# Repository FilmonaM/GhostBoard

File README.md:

# GhostBoard

A 66‑key custom, hot‑swappable mechanical keyboard built around the RP2040 MCU and a USB‑C port.

## Key Features
- **Hot‑swappable sockets** (MX) allow you to change switches whenever you want without soldering.  
- Compact 66‑key layout inspired by Keychron’s design.  
- Fully two‑layer PCB with bottom‑side routing for a clean top surface.  

## Layout
Here’s the final Keyboard Layout Editor (KLE) grid I used for my 66‑key design:

## PCB
After routing all rows and columns on the bottom layer and placing 66 hot‑swap footprints on top, this is the final PCB:

## Case & CAD
The case was made in onshape and includes a cutout for the usbc port:

## BOM

| Components                     | Quantity | Price (USD) | Link                                      |
|--------------------------------|----------|-------------|-------------------------------------------|
|all the discrete components| bulk     | around $10 USD   | all from JLCPCB|
| Hot‑swap sockets (Cherry MX)   | 66       | $14 USD       | [from amazon](https://www.amazon.com/DUROCK-Mechanical-Keyboard-Switches-Hot-Swap/dp/B0B4W9YMGM?th=1)                                     |
| Cherry MX Brown switches       | 66       | $50 USD       | [from amazaon](https://www.amazon.com/Switches-Mechanical-Keyboards-Mounted-MX1AG1NA/dp/B09ZSR5WKH/ref=sr_1_1?crid=25HJUXP1OSN6J&dib=eyJ2IjoiMSJ9.JCXKItNl7G_bBJpSwKUJq664n-BOf2YbUH0WZa7hDmZxRafbLwI-glj977bGbt29tDvCveNze3P3gqmgoAn0l3rlchmQZ61RmHV2XPem3Jz3tot1azwV7jrsNV-PzRqVyuHCwUeeXaebcL0bObmG1d8kziBrCC7ZMtnRtgIo-ddwnsvz2wgowiUgUF-HD41rfdkHTE_UOYzvFpoSButMwc7_yddFstvRSoyNQbJw2ynUmxFPIG3dxOFQfZoTBf_ieIKHUoq1lWhQpLDM12rkFp4_vQ0Xz3IjDz0DVBT-efY.RL9APB_ELO4EKoe-h864Dvl7o-cF4AvWYBAotoN6pFo&dib_tag=se&keywords=cherry%2Bmx%2Bswitches%2Bbrown&qid=1753349383&s=electronics&sprefix=cherry%2Bmx%2Bswitches%2Bbrow%2Celectronics%2C191&sr=1-1&th=1)                                    |
| Stabilizer kit                 | 1        | $19 USD       | [from amazon](https://www.amazon.com/Keyboard-Stabilizers-Mechanical-Keyboards-Switches/dp/B0D2R13N2N/ref=sr_1_1_sspa?crid=2UC7ED8DWWUDM&dib=eyJ2IjoiMSJ9.P4sTVbDzkYqSr2Qe2aEKgUz9OjRmws6DREJdi517d7j9yxmY-mCmIoPxXbUmOFQNayDjFH5Sx7xpnLaN4KOjDOL0SpdCwoeUz22PRWkEPbsXPuUcYROyJJAhYlPQDTz6njqvp06jBaKfk85rN3X2qAGkjYN52kWKGrqK5ZmzdgV61Xb8_8AqggnEFYknCTHt.kM48GyCD-8_UloBzSZMtd7l1z-blnw8Z4I1GEPk9-0M&dib_tag=se&keywords=mx%2Bstabs&qid=1753349468&s=electronics&sprefix=mx%2Bstabs%2Celectronics%2C166&sr=1-1-spons&sp_csd=d2lkZ2V0TmFtZT1zcF9hdGY&th=1)
| RP2040 MCU board- usbc           | 1        | $1.20        | [amazon link](https://www.amazon.com/RP2040-Board-Type-C-Raspberry-Micropython/dp/B0CG9FWDDC?th=1) |
| PCBs (×5, incl. shipping & tax) | 5        | $29.29       | using jlcpcb                               |

total price = $119.49

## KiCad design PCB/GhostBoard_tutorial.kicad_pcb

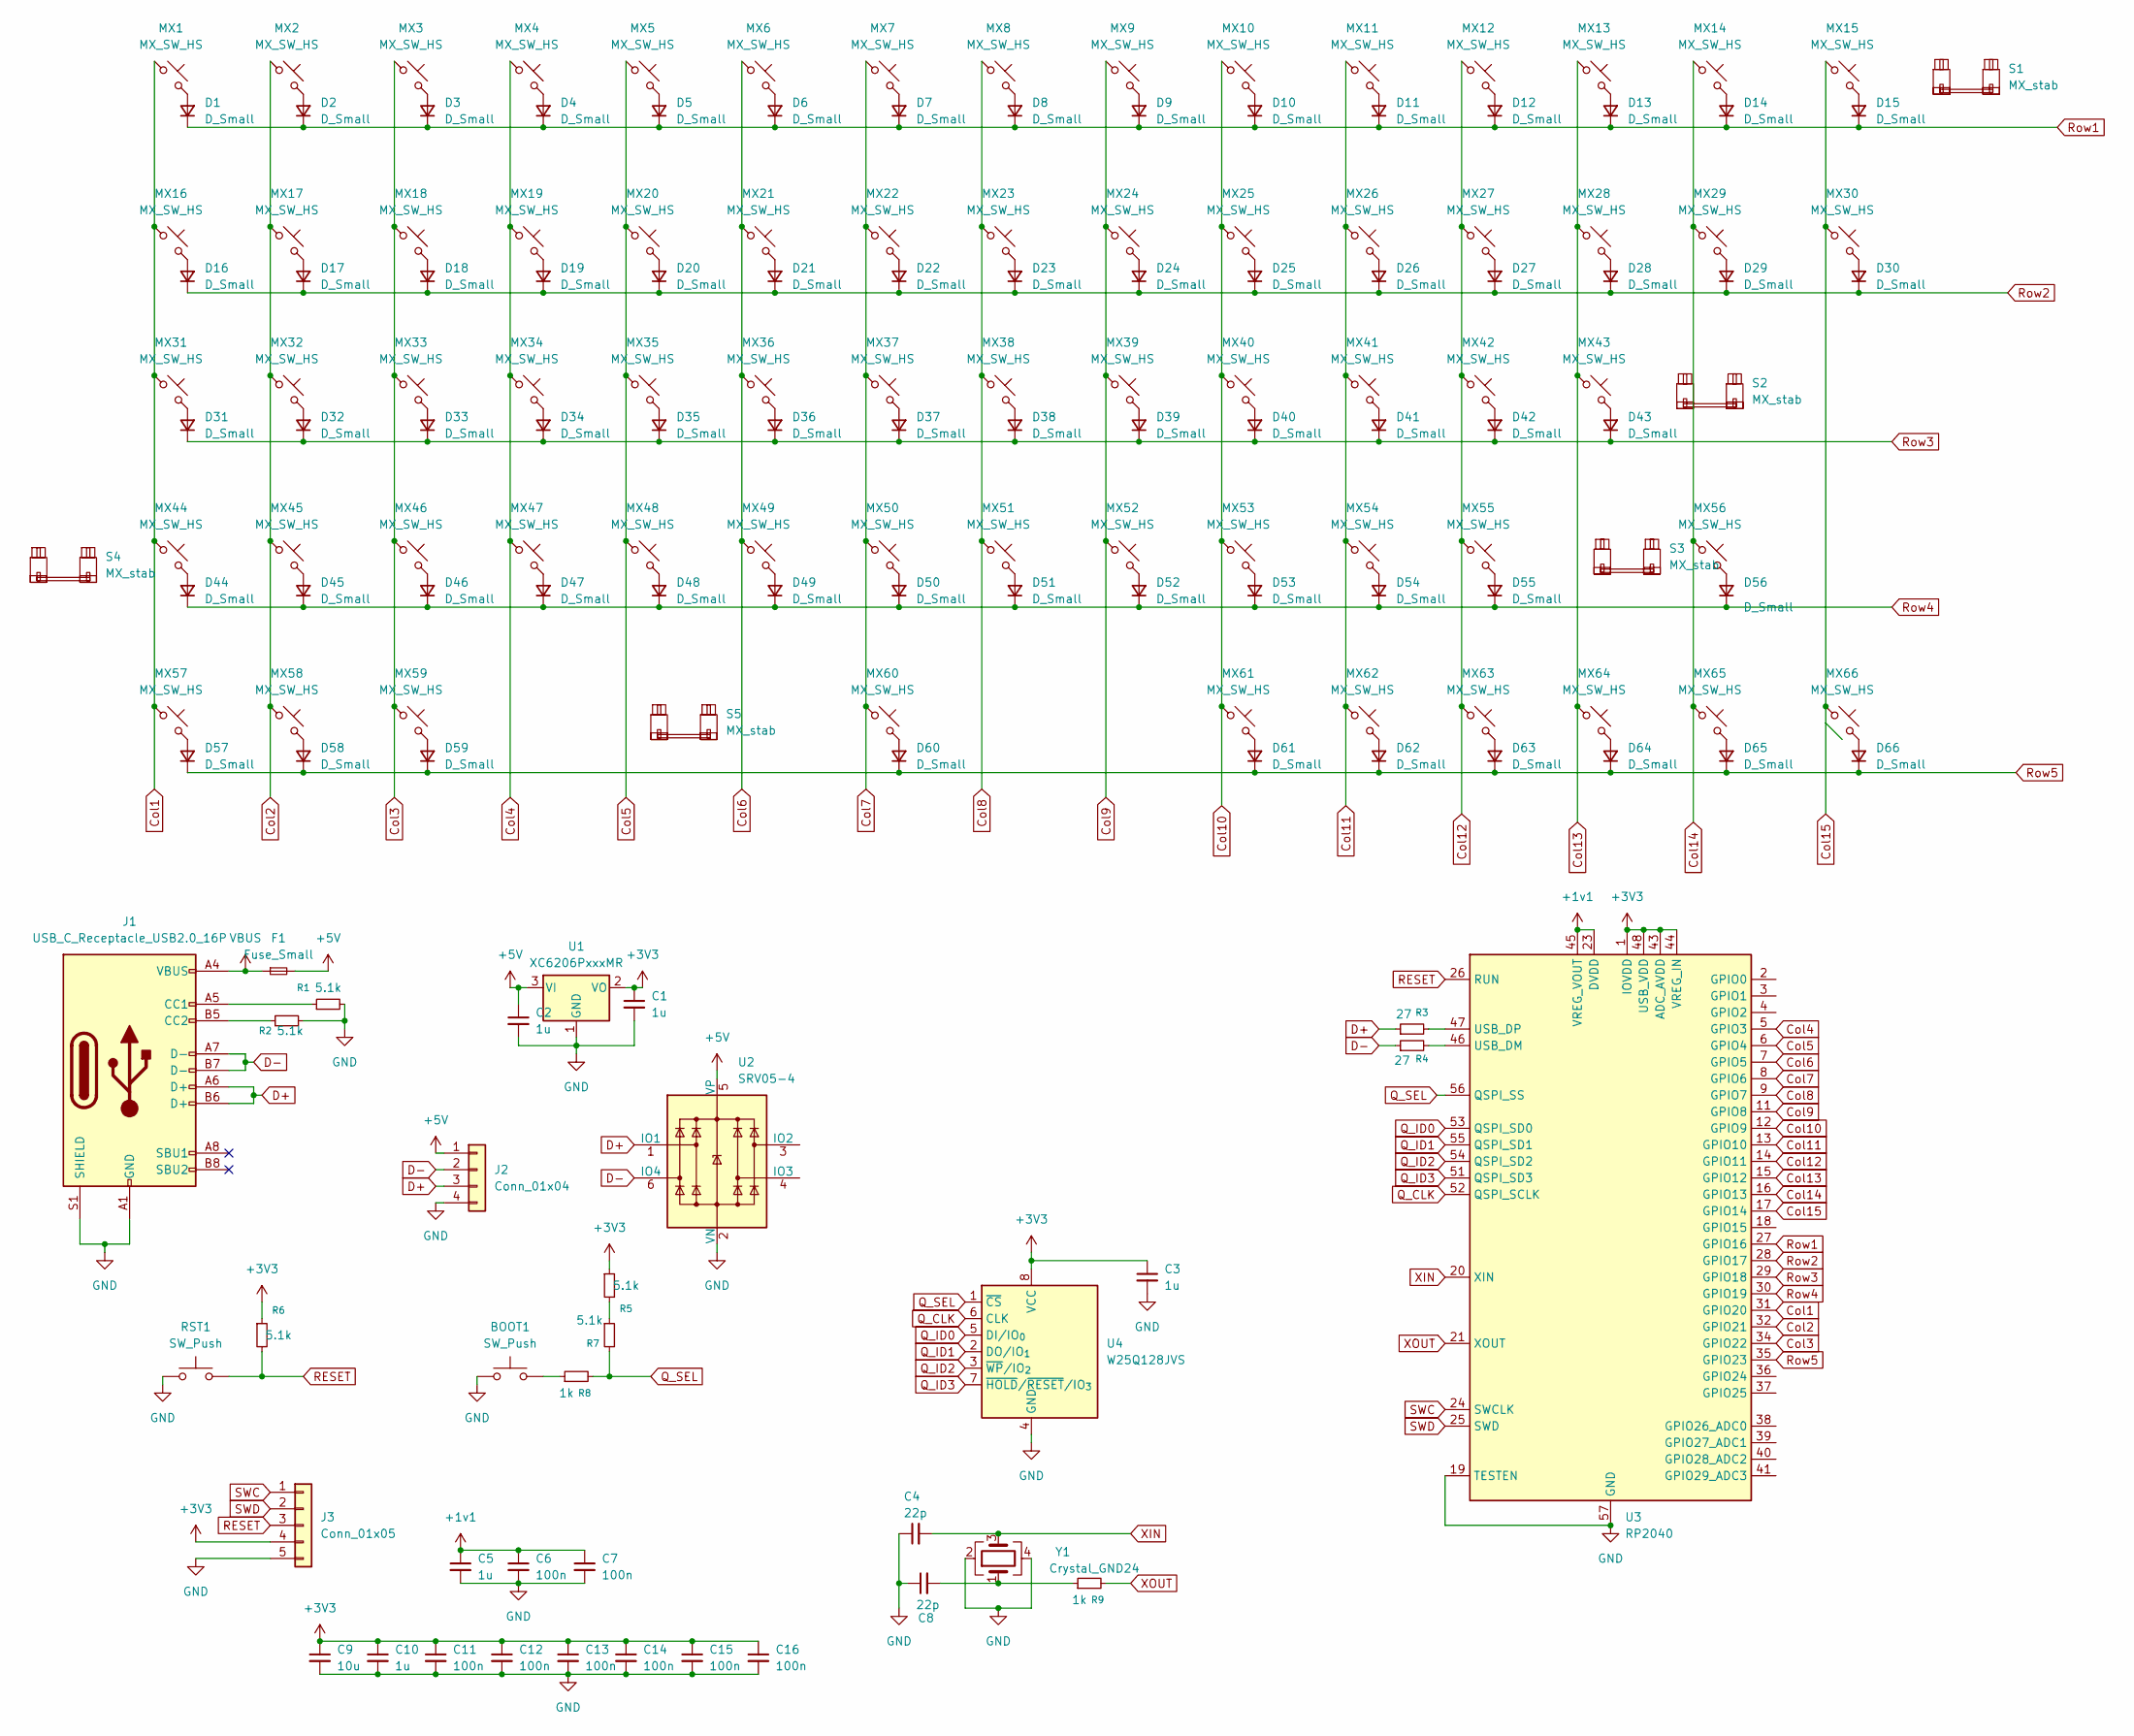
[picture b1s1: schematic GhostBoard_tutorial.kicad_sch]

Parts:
BOOT1: SW_Push; SW_SPST_TL3342
C1, C2, C3, C5, C10: 1u; C_0402_1005Metric
C4, C8: 22p; C_0402_1005Metric
C6, C7, C11, C12, C13, C14, C15, C16: 100n; C_0402_1005Metric
C9: 10u; C_0603_1608Metric
D1, D2, D3, D4, D5, D6, D7, D8, D9, D10, D11, D12, D13, D14, D15, D16, D17, D18, D19, D20, D21, D22, D23, D24, D25, D26, D27, D28, D29, D30, D31, D32, D33, D34, D35, D36, D37, D38, D39, D40, D41, D42, D43, D44, D45, D46, D47, D48, D49, D50, D51, D52, D53, D54, D55, D56, D57, D58, D59, D60, D61, D62, D63, D64, D65, D66: D_Small; D_SOD-123
F1: Fuse_Small; Fuse_1206_3216Metric
J1: USB_C_Receptacle_USB2.0_16P; USB_C_Receptacle_HRO_TYPE-C-31-M-12
J2: Conn_01x04; JST_SH_SM04B-SRSS-TB_1x04-1MP_P1.00mm_Horizontal
J3: Conn_01x05; PinHeader_1x05_P2.54mm_Vertical
MX1, MX2, MX3, MX4, MX5, MX6, MX7, MX8, MX9, MX10, MX11, MX12, MX13, MX14, MX15, MX17, MX18, MX19, MX20, MX21, MX22, MX23, MX24, MX25, MX26, MX27, MX28, MX30, MX32, MX33, MX34, MX35, MX36, MX37, MX38, MX39, MX40, MX41, MX42, MX43, MX44, MX45, MX46, MX47, MX48, MX49, MX50, MX51, MX52, MX53, MX54, MX55, MX56, MX58, MX60, MX64, MX65, MX66: MX_SW_HS; SW_MX_HS_CPG151101S11_1u
MX16, MX29: MX_SW_HS; SW_MX_HS_CPG151101S11_1.5u
MX31: MX_SW_HS; SW_MX_HS_CPG151101S11_1.75u
MX57, MX59, MX61, MX62, MX63: MX_SW_HS; SW_MX_HS_CPG151101S11_1.25u
R1, R2, R5, R6, R7: 5.1k; R_0402_1005Metric
R3, R4: 27; R_0402_1005Metric
R8, R9: 1k; R_0402_1005Metric
RST1: SW_Push; SW_SPST_TL3342
S1: MX_stab; STAB_MX_P_2u
S2, S3, S4: MX_stab; STAB_MX_P_2.25u
S5: MX_stab; STAB_MX_P_6.25u
U1: XC6206PxxxMR; SOT-23-3
U2: SRV05-4; SOT-23-6-routable
U3: RP2040; QFN-56-1EP_7x7mm_P0.4mm_EP3.2x3.2mm
U4: W25Q128JVS; SOIC-8_5.3x5.3mm_P1.27mm
Y1: Crystal_GND24; Crystal_SMD_3225-4Pin_3.2x2.5mm

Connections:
+5V: C2.1, F1.2, J2.1, U1.3 (VI), U2.5 (VP)
Col1: MX1.1, MX16.1, MX31.1, MX44.1, MX57.1, U3.31 (GPIO20)
Col2: MX2.1, MX17.1, MX32.1, MX45.1, MX58.1, U3.32 (GPIO21)
Col3: MX3.1, MX18.1, MX33.1, MX46.1, MX59.1, U3.34 (GPIO22)
Col4: MX4.1, MX19.1, MX34.1, MX47.1, U3.5 (GPIO3)
Col5: MX5.1, MX20.1, MX35.1, MX48.1, U3.6 (GPIO4)
Col6: MX6.1, MX21.1, MX36.1, MX49.1, U3.7 (GPIO5)
Col7: MX7.1, MX22.1, MX37.1, MX50.1, MX60.1, U3.8 (GPIO6)
Col8: MX8.1, MX23.1, MX38.1, MX51.1, U3.9 (GPIO7)
Col9: MX9.1, MX24.1, MX39.1, MX52.1, U3.11 (GPIO8)
Col10: MX10.1, MX25.1, MX40.1, MX53.1, MX61.1, U3.12 (GPIO9)
Col11: MX11.1, MX26.1, MX41.1, MX54.1, MX62.1, U3.13 (GPIO10)
Col12: MX12.1, MX27.1, MX42.1, MX55.1, MX63.1, U3.14 (GPIO11)
Col13: MX13.1, MX28.1, MX43.1, MX64.1, U3.15 (GPIO12)
Col14: MX14.1, MX29.1, MX56.1, MX65.1, U3.16 (GPIO13)
Col15: MX15.1, MX30.1, MX66.1, U3.17 (GPIO14)
D+: J1.A6 (D+), J1.B6 (D+), J2.3, R3.1, U2.1 (IO1)
D-: J1.A7 (D-), J1.B7 (D-), J2.2, R4.1, U2.6 (IO4)
unnamed: BOOT1.2, R8.1
unnamed: D1.2 (A), MX1.2
unnamed: D2.2 (A), MX2.2
unnamed: D3.2 (A), MX3.2
unnamed: D4.2 (A), MX4.2
unnamed: D5.2 (A), MX5.2
unnamed: D6.2 (A), MX6.2
unnamed: D7.2 (A), MX7.2
unnamed: D8.2 (A), MX8.2
unnamed: D9.2 (A), MX9.2
unnamed: D10.2 (A), MX10.2
unnamed: D11.2 (A), MX11.2
unnamed: D12.2 (A), MX12.2
unnamed: D13.2 (A), MX13.2
unnamed: D14.2 (A), MX14.2
unnamed: D15.2 (A), MX15.2
unnamed: D16.2 (A), MX16.2
unnamed: D17.2 (A), MX17.2
unnamed: D18.2 (A), MX18.2
unnamed: D19.2 (A), MX19.2
unnamed: D20.2 (A), MX20.2
unnamed: D21.2 (A), MX21.2
unnamed: D22.2 (A), MX22.2
unnamed: D23.2 (A), MX23.2
unnamed: D24.2 (A), MX24.2
unnamed: D25.2 (A), MX25.2
unnamed: D26.2 (A), MX26.2
unnamed: D27.2 (A), MX27.2
unnamed: D28.2 (A), MX28.2
unnamed: D29.2 (A), MX29.2
unnamed: D30.2 (A), MX30.2
unnamed: D31.2 (A), MX31.2
unnamed: D32.2 (A), MX32.2
unnamed: D33.2 (A), MX33.2
unnamed: D34.2 (A), MX34.2
unnamed: D35.2 (A), MX35.2
unnamed: D36.2 (A), MX36.2
unnamed: D37.2 (A), MX37.2
unnamed: D38.2 (A), MX38.2
unnamed: D39.2 (A), MX39.2
unnamed: D40.2 (A), MX40.2
unnamed: D41.2 (A), MX41.2
unnamed: D42.2 (A), MX42.2
unnamed: D43.2 (A), MX43.2
unnamed: D44.2 (A), MX44.2
unnamed: D45.2 (A), MX45.2
unnamed: D46.2 (A), MX46.2
unnamed: D47.2 (A), MX47.2
unnamed: D48.2 (A), MX48.2
unnamed: D49.2 (A), MX49.2
unnamed: D50.2 (A), MX50.2
unnamed: D51.2 (A), MX51.2
unnamed: D52.2 (A), MX52.2
unnamed: D53.2 (A), MX53.2
unnamed: D54.2 (A), MX54.2
unnamed: D55.2 (A), MX55.2
unnamed: D56.2 (A), MX56.2
unnamed: D57.2 (A), MX57.2
unnamed: D58.2 (A), MX58.2
unnamed: D59.2 (A), MX59.2
unnamed: D60.2 (A), MX60.2
unnamed: D61.2 (A), MX61.2
unnamed: D62.2 (A), MX62.2
unnamed: D63.2 (A), MX63.2
unnamed: D64.2 (A), MX64.2
unnamed: D65.2 (A), MX65.2
unnamed: D66.2 (A), MX66.2
unnamed: J1.A5 (CC1), R1.1
unnamed: J1.B5 (CC2), R2.1
unnamed: R5.2, R7.1
unnamed: R4.2, U3.46 (USB_DM)
unnamed: R3.2, U3.47 (USB_DP)
Q_CLK: U3.52 (QSPI_SCLK), U4.6 (CLK)
Q_ID0: U3.53 (QSPI_SD0), U4.5 (DI/IO_{0})
Q_ID1: U3.55 (QSPI_SD1), U4.2 (DO/IO_{1})
Q_ID2: U3.54 (QSPI_SD2), U4.3 (~WP/IO_{2})
Q_ID3: U3.51 (QSPI_SD3), U4.7 (~HOLD/~RESET/IO_{3})
Q_SEL: R7.2, R8.2, U3.56 (QSPI_SS), U4.1 (~CS)
RESET: J3.3, R6.2, RST1.2, U3.26 (RUN)
Row1: D1.1 (K), D2.1 (K), D3.1 (K), D4.1 (K), D5.1 (K), D6.1 (K), D7.1 (K), D8.1 (K), D9.1 (K), D10.1 (K), D11.1 (K), D12.1 (K), D13.1 (K), D14.1 (K), D15.1 (K), U3.27 (GPIO16)
Row2: D16.1 (K), D17.1 (K), D18.1 (K), D19.1 (K), D20.1 (K), D21.1 (K), D22.1 (K), D23.1 (K), D24.1 (K), D25.1 (K), D26.1 (K), D27.1 (K), D28.1 (K), D29.1 (K), D30.1 (K), U3.28 (GPIO17)
Row3: D31.1 (K), D32.1 (K), D33.1 (K), D34.1 (K), D35.1 (K), D36.1 (K), D37.1 (K), D38.1 (K), D39.1 (K), D40.1 (K), D41.1 (K), D42.1 (K), D43.1 (K), U3.29 (GPIO18)
Row4: D44.1 (K), D45.1 (K), D46.1 (K), D47.1 (K), D48.1 (K), D49.1 (K), D50.1 (K), D51.1 (K), D52.1 (K), D53.1 (K), D54.1 (K), D55.1 (K), D56.1 (K), U3.30 (GPIO19)
Row5: D57.1 (K), D58.1 (K), D59.1 (K), D60.1 (K), D61.1 (K), D62.1 (K), D63.1 (K), D64.1 (K), D65.1 (K), D66.1 (K), U3.35 (GPIO23)
SWC: J3.1, U3.24 (SWCLK)
SWD: J3.2, U3.25 (SWD)
VBUS: F1.1, J1.A4 (VBUS), J1.A9 (VBUS), J1.B4 (VBUS), J1.B9 (VBUS)
XOUT: R9.2, U3.21 (XOUT)

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
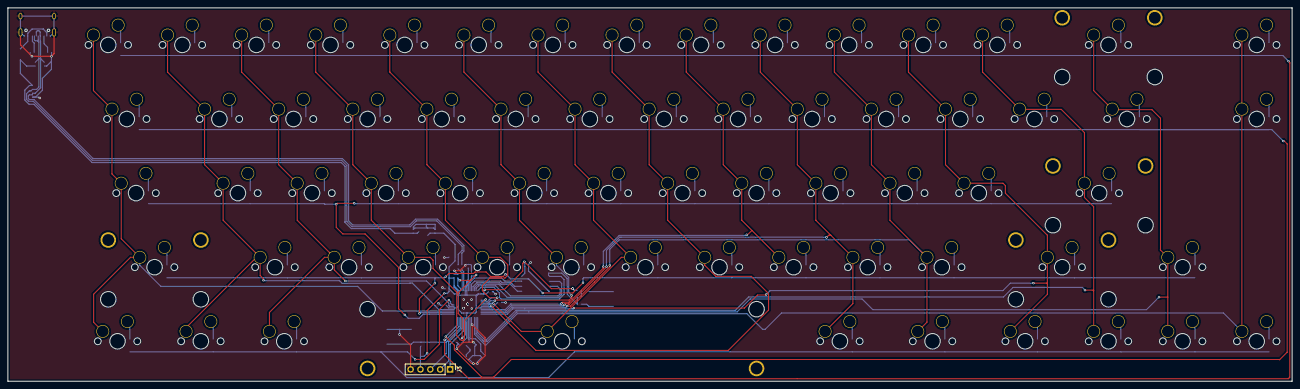
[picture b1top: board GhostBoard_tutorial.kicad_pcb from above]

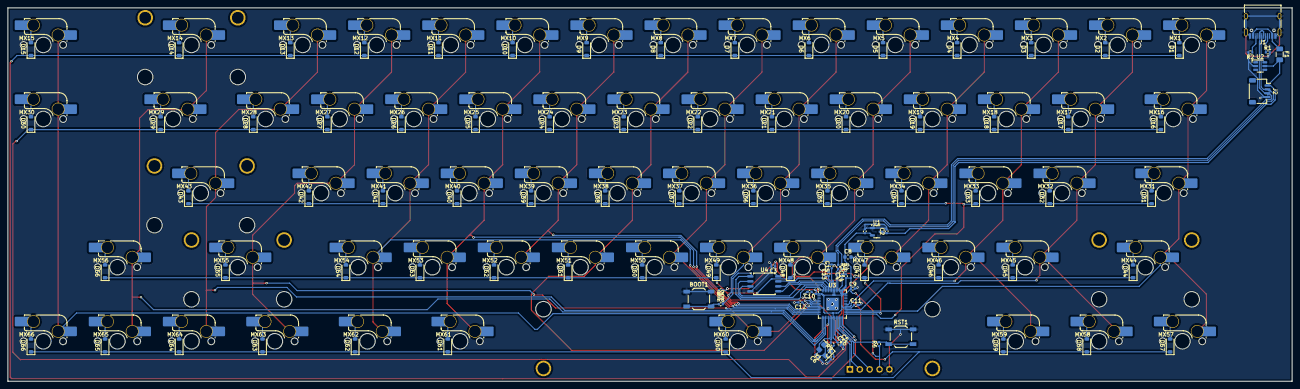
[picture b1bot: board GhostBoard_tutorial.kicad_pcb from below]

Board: 2 copper layers, 330.2 x 96.0 mm, 173 parts (167 on the bottom side), 111 nets.

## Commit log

2025-07-24 updated bom
2025-07-24 giving the BOM a clearer name
2025-07-25 adding BOM to README
2025-07-30 Finishing touches and improving cad
2025-07-30 finishing touches v2
2025-07-31 improving the keyboard design some more
2025-07-31 new image and updating the README
2025-08-07 New PCB
2025-08-14 updated images, and bom
